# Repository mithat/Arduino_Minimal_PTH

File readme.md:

Arduino_Minimal_PTH
===================

Crazy stupid experiment to see how small you can make an Arduino-compatible
board using through-hole parts.

The design is based on the 
[Arduino Pro Mini](http://arduino.cc/en/Main/arduinoBoardProMini), and it tries
to follow that board's I/O conventions. Everything that can be considered 
optional has been eliminated.

Made with [KiCad](http://www.kicad-pcb.org/), which is [free and open source software](http://en.wikipedia.org/wiki/Free_and_open-source_software).
No raptors were touched in the making of this board.

No, I haven't built it (yet?).

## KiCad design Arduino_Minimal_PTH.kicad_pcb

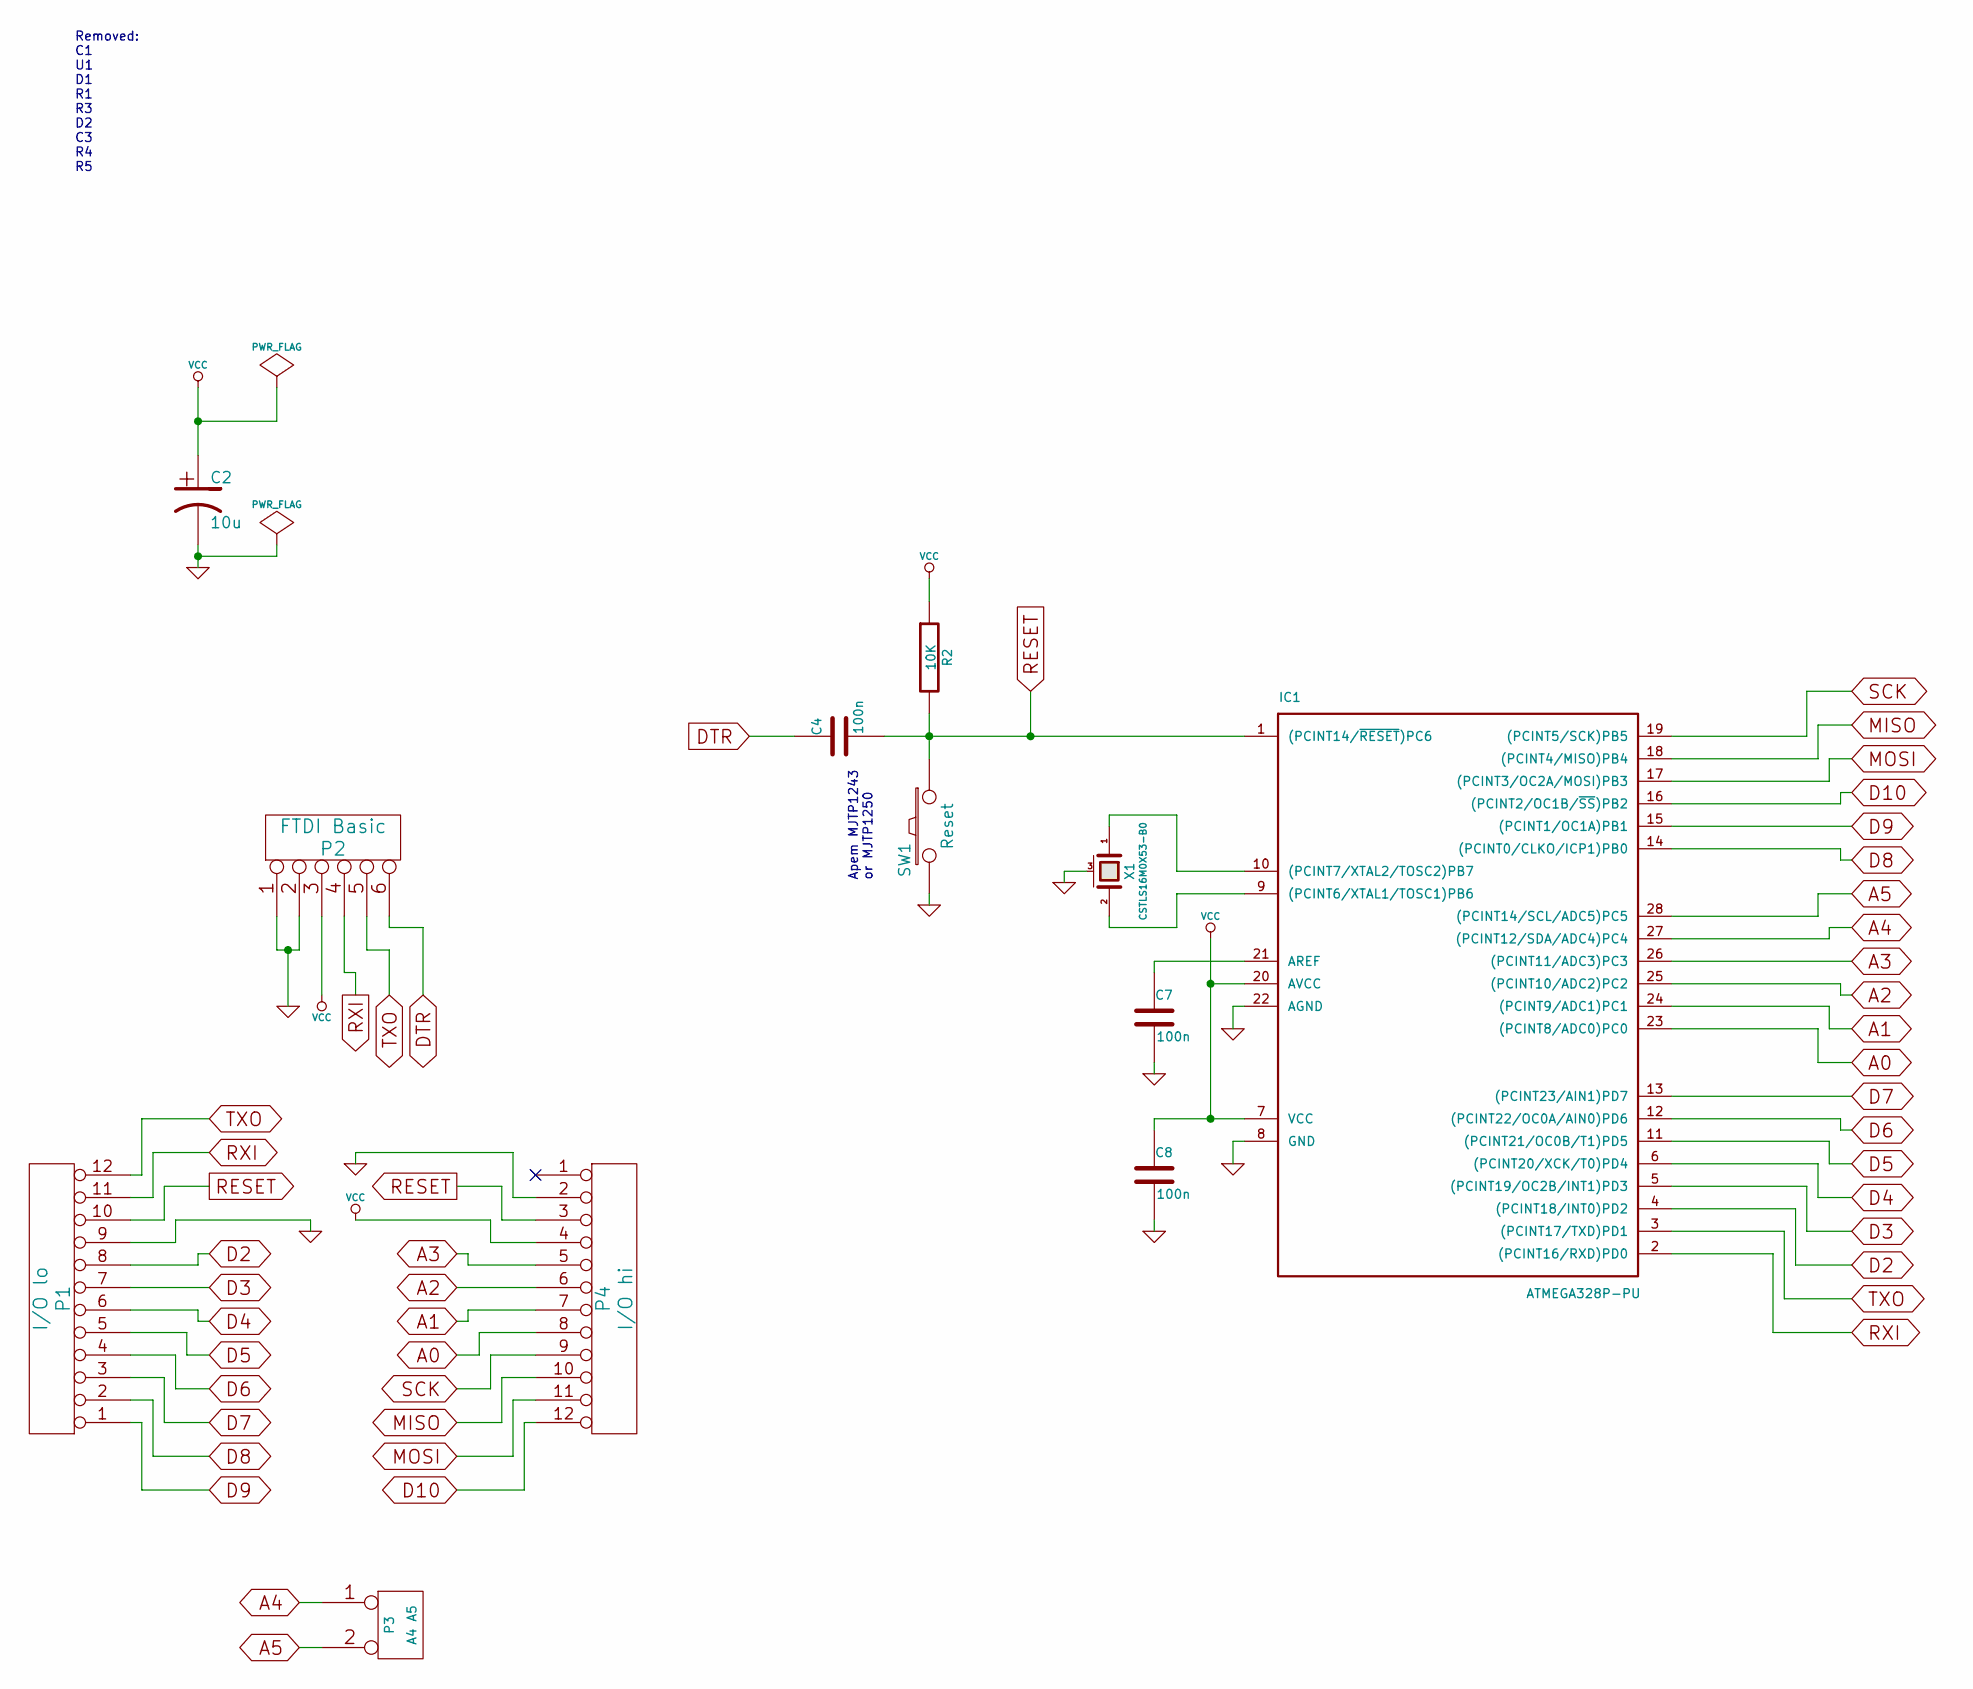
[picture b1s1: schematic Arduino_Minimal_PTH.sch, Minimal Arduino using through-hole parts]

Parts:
C2: 10u; mfk-CRP_4.0_2.5_0.5
C4, C7, C8: 100n; mfk-C_4.0_2.5_2.5_0.5
IC1: ATMEGA328P-PU; mfk-DIP-28_300_rnd
P1: I/O lo; mfk-SIL-12
P2: FTDI Basic; mfk-SIL-6
P3: A4 A5; mfk-SIL-2
P4: I/O hi; mfk-SIL-12
R2: 10K; mfk-R_0.25W_RN55_vert
SW1: Reset; mfk-SW_PUSH_6x3.5mm
X1: CSTLS16M0X53-B0; mfk-Murata-CSTLS_X

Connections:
A0: IC1.23 ((PCINT8/ADC0)PC0), P4.8
A1: IC1.24 ((PCINT9/ADC1)PC1), P4.7
A2: IC1.25 ((PCINT10/ADC2)PC2), P4.6
A3: IC1.26 ((PCINT11/ADC3)PC3), P4.5
A4: IC1.27 ((PCINT12/SDA/ADC4)PC4), P3.1
A5: IC1.28 ((PCINT14/SCL/ADC5)PC5), P3.2 (PM)
D2: IC1.4 ((PCINT18/INT0)PD2), P1.8
D3: IC1.5 ((PCINT19/OC2B/INT1)PD3), P1.7
D4: IC1.6 ((PCINT20/XCK/T0)PD4), P1.6
D5: IC1.11 ((PCINT21/OC0B/T1)PD5), P1.5
D6: IC1.12 ((PCINT22/OC0A/AIN0)PD6), P1.4
D7: IC1.13 ((PCINT23/AIN1)PD7), P1.3
D8: IC1.14 ((PCINT0/CLKO/ICP1)PB0), P1.2
D9: IC1.15 ((PCINT1/OC1A)PB1), P1.1
D10: IC1.16 ((PCINT2/OC1B/~SS~)PB2), P4.12
DTR: C4.1, P2.6
GND: C2.2, C7.2, C8.2, IC1.8 (GND), IC1.22 (AGND), P1.9, P2.1, P2.2, P4.2, SW1.2, X1.3 (case)
MISO: IC1.18 ((PCINT4/MISO)PB4), P4.10
MOSI: IC1.17 ((PCINT3/OC2A/MOSI)PB3), P4.11
unnamed: IC1.10 ((PCINT7/XTAL2/TOSC2)PB7), X1.1
unnamed: IC1.9 ((PCINT6/XTAL1/TOSC1)PB6), X1.2
unnamed: C7.1, IC1.21 (AREF)
RESET: C4.2, IC1.1 ((PCINT14/~RESET~)PC6), P1.10, P4.3, R2.2, SW1.1
RXI: IC1.2 ((PCINT16/RXD)PD0), P1.11, P2.4
SCK: IC1.19 ((PCINT5/SCK)PB5), P4.9
TXO: IC1.3 ((PCINT17/TXD)PD1), P1.12, P2.5
VCC: C2.1, C8.1, IC1.7 (VCC), IC1.20 (AVCC), P2.3, P4.4, R2.1

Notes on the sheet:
Apem MJTP1243 or MJTP1250
Removed: C1 U1 D1 R1 R3 D2 C3 R4 R5

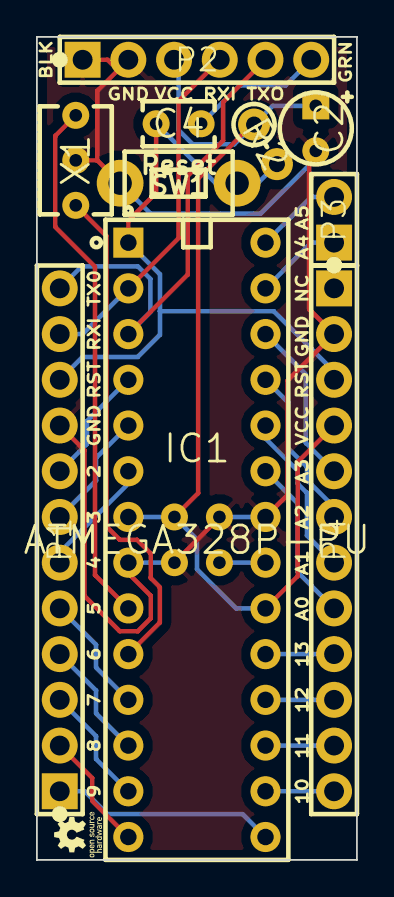
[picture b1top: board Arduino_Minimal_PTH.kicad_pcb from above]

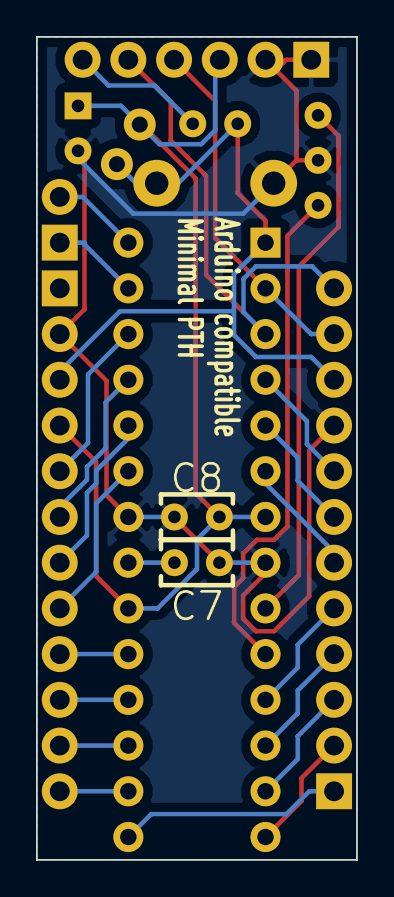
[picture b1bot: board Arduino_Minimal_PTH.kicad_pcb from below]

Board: 2 copper layers, 17.8 x 45.7 mm, 13 parts (2 on the bottom side), 27 nets.

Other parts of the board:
VAL: REF; oshw-logo-100mil-FSilk

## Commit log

2015-03-26 Fork from Arduino_Pro_Mini_PTH.
2015-03-26 Placed.
2015-03-26 Routed
2015-03-26 Rerouted.
2015-03-26 Flooded.
2015-03-26 Silkscreen optimizations.
2015-03-26 Silkscreen tweaks.
2015-03-26 Added documentation images to readme.
2015-03-26 Readme revisions.
2015-03-26 Readme syntax error fix.
2015-04-04 Renamed doc -> docs.
2015-04-04 Modified .gitignore to exclude only top-level pdf, zip, and svg files.

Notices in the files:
Arduino_Minimal_PTH.kicad_pcb:
Creative Commons Attribution Share Alike 3.0 License
